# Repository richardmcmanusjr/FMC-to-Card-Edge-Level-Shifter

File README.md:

# FMC-to-Card-Edge-Level-Shifter

This repository contains an 88 channel conversion board designed to interface an 88-pin probe card with a Virtex-7 VC707 FPGA via an FMC cable. Level shifting was required to lower the FPGA's 1.8V logic to 1.2V. Resistor voltage dividers were chosen for this purpose.

# V3.1

- Resistor arrays used for voltage dividers
- Male header pins oriented at right angle to FMC connector
- Low quiescent current regulator implemented for 1.2V power supply
- Jumper for selecting power from FPGA or SMA

## Design

## Layout 

# V2

- Discrete 0603 resistors used for voltage dividers
- Card edge connector oriented at right angle to FMC connector
- Optional SMAs for GND and Power
 
## Design

## Layout

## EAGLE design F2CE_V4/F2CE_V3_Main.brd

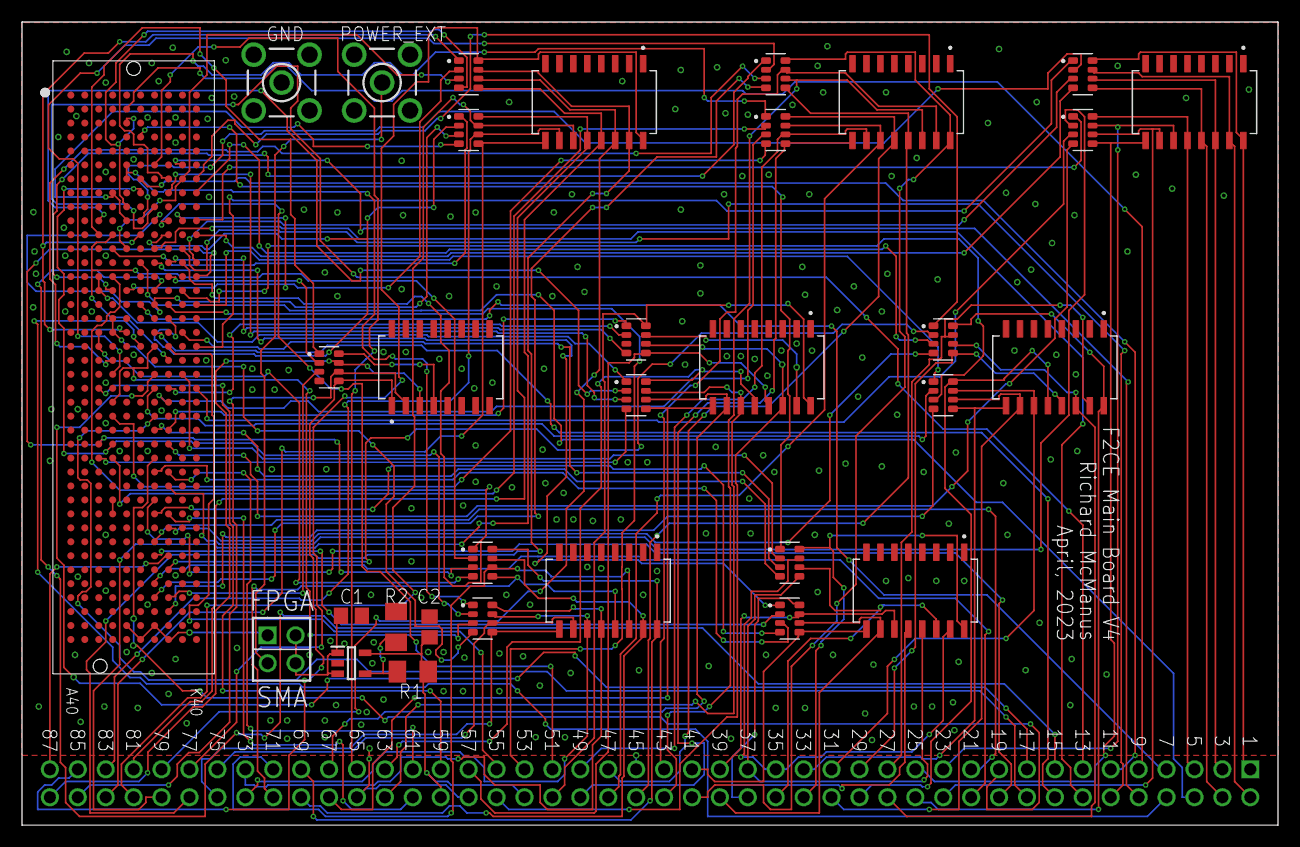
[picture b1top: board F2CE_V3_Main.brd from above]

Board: 2 copper layers, 114.3 x 73.1 mm, 33 parts (0 on the bottom side), 150 nets.

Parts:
4BITVD1:R1, 8BITVD1:R1, 8BITVD1:R2, 8BITVD2:R1, 8BITVD2:R2, 8BITVD3:R1, 8BITVD3:R2, 8BITVD4:R1, 8BITVD4:R2, 8BITVD5:R1, 8BITVD5:R2, 8BITVD6:R1, 8BITVD6:R2, 8BITVD7:R1, 8BITVD7:R2: YC164-FR-0760R4L; RESCAXE80P320X160X70-8N
4BITVD1:RN1, 8BITVD1:RN1, 8BITVD2:RN1, 8BITVD3:RN1, 8BITVD4:RN1, 8BITVD5:RN1, 8BITVD6:RN1, 8BITVD7:RN1: 4816P-1-121LF; SOIC127P762X240-16N
C1, C2: 1 uF; C0805
GND: LTI-SASF54GT
IC1: ADP171AUJZ-R7; SOT95P280X100-5N
J1: 88-PIN-HEADER
J2: ASP-134602-01; ASP13460201
J3: 70287-1098; HDRV4W64P254_2X2_521X508X851P
POWER_EXT: LTI-SASF54GT
R1: 510; M1206
R2: 360; M1206

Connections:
4BITVD1:OUT3: 4BITVD1:R1.8, 4BITVD1:RN1.4
8BITVD5:OUT1: 8BITVD5:R1.7, 8BITVD5:RN1.15
C10: 8BITVD5:R2.2, J2.C10
C11: 4BITVD1:R1.1, J2.C11
C14&C15: 8BITVD5:R2.1, J2.C14, J2.C15
C18&C19: 8BITVD6:R1.4, J2.C18, J2.C19
C22: J1.59, J2.C22
C26&K14: 8BITVD6:R1.3, J2.C26, J2.K14
C27: 8BITVD5:R2.4, J2.C27
CS10: 8BITVD5:R2.6, 8BITVD5:RN1.10, J1.67
CS11: 4BITVD1:R1.5, 4BITVD1:RN1.1, J1.85
CS14&CS15: 8BITVD5:R2.5, 8BITVD5:RN1.9, J1.68
CS18&CS19: 8BITVD6:R1.8, 8BITVD6:RN1.16, J1.69
CS26&KS14: 8BITVD6:R1.7, 8BITVD6:RN1.15, J1.70
CS27: 8BITVD5:R2.8, 8BITVD5:RN1.12, J1.63
D8&E10: 8BITVD7:R2.4, J2.D8, J2.E10
D11&H20: 8BITVD6:R1.2, J2.D11, J2.H20
D12: 8BITVD7:R2.1, J2.D12
D14&J13: 8BITVD6:R1.1, J2.D14, J2.J13
D15: 8BITVD4:R1.1, J2.D15
D17&D18: 8BITVD6:R2.4, J2.D17, J2.D18
D20: 8BITVD4:R1.3, J2.D20
D21: 8BITVD4:R1.2, J2.D21
D23&G19: 8BITVD6:R2.3, J2.D23, J2.G19
D24: 8BITVD4:R2.4, J2.D24
D26&F8: 8BITVD6:R2.2, J2.D26, J2.F8
D27: 8BITVD4:R2.2, J2.D27
DS8&ES10: 8BITVD7:R2.8, 8BITVD7:RN1.12, J1.81
DS11&HS20: 8BITVD6:R1.6, 8BITVD6:RN1.14, J1.71
DS12: 8BITVD7:R2.5, 8BITVD7:RN1.9, J1.84
DS14&JS13: 8BITVD6:R1.5, 8BITVD6:RN1.13, J1.72
DS15: 8BITVD4:R1.5, 8BITVD4:RN1.13, J1.46
DS17&DS18: 8BITVD6:R2.8, 8BITVD6:RN1.12, J1.73
DS20: 8BITVD4:R1.7, 8BITVD4:RN1.15, J1.43
DS21: 8BITVD4:R1.6, 8BITVD4:RN1.14, J1.44
DS23&GS19: 8BITVD6:R2.7, 8BITVD6:RN1.11, J1.74
DS24: 8BITVD4:R2.8, 8BITVD4:RN1.12, J1.47
DS26&FS8: 8BITVD6:R2.6, 8BITVD6:RN1.10, J1.75
DS27: 8BITVD4:R2.6, 8BITVD4:RN1.10, J1.49
E2: J1.9, J2.E2
E6&E7: 8BITVD6:R2.1, J2.E6, J2.E7
E9&E3: 8BITVD7:R1.4, J2.E3, J2.E9
E12&J7: 8BITVD7:R1.3, J2.E12, J2.J7
E15&J10: 8BITVD7:R1.2, J2.E15, J2.J10
E18&F11: 8BITVD7:R1.1, J2.E18, J2.F11
ES6&ES7: 8BITVD6:R2.5, 8BITVD6:RN1.9, J1.76
ES9&ES3: 8BITVD7:R1.8, 8BITVD7:RN1.16, J1.77
ES12&JS7: 8BITVD7:R1.7, 8BITVD7:RN1.15, J1.78
ES15&JS10: 8BITVD7:R1.6, 8BITVD7:RN1.14, J1.79
ES18&FS11: 8BITVD7:R1.5, 8BITVD7:RN1.13, J1.80
F4: 8BITVD3:R1.1, J2.F4
F7: J1.11, J2.F7
F10: 8BITVD1:R1.2, J2.F10
F13: J1.6, J2.F13
F16: J1.7, J2.F16
F19: J1.8, J2.F19
FS4: 8BITVD3:R1.5, 8BITVD3:RN1.13, J1.37
FS10: 8BITVD1:R1.6, 8BITVD1:RN1.14, J1.3
G6: J1.65, J2.G6
G9: J1.13, J2.G9
G10&G16: 8BITVD7:R2.3, J2.G10, J2.G16
G12: J1.14, J2.G12
G13: 8BITVD3:R2.1, J2.G13
G15: J1.15, J2.G15
G18: J1.16, J2.G18
G21: J1.17, J2.G21
G22: 8BITVD2:R2.2, J2.G22
G24: J1.18, J2.G24
G25: 8BITVD3:R1.4, J2.G25
G27: J1.19, J2.G27
G28: 8BITVD3:R2.3, J2.G28
G30: J1.20, J2.G30
G31: 8BITVD3:R2.4, J2.G31
G33: J1.21, J2.G33
G34: 8BITVD3:R2.2, J2.G34
G36: J1.22, J2.G36
G37: 8BITVD4:R1.4, J2.G37
GND: 4BITVD1:RN1.13, 4BITVD1:RN1.14, 4BITVD1:RN1.15, 4BITVD1:RN1.16, 8BITVD1:RN1.1, 8BITVD1:RN1.2, 8BITVD1:RN1.3, 8BITVD1:RN1.4, 8BITVD1:RN1.5, 8BITVD1:RN1.6, 8BITVD1:RN1.7, 8BITVD1:RN1.8, 8BITVD2:RN1.1, 8BITVD2:RN1.2, 8BITVD2:RN1.3, 8BITVD2:RN1.4, 8BITVD2:RN1.5, 8BITVD2:RN1.6, 8BITVD2:RN1.7, 8BITVD2:RN1.8, 8BITVD3:RN1.1, 8BITVD3:RN1.2, 8BITVD3:RN1.3, 8BITVD3:RN1.4, 8BITVD3:RN1.5, 8BITVD3:RN1.6, 8BITVD3:RN1.7, 8BITVD3:RN1.8, 8BITVD4:RN1.1, 8BITVD4:RN1.2, 8BITVD4:RN1.3, 8BITVD4:RN1.4, 8BITVD4:RN1.5, 8BITVD4:RN1.6, 8BITVD4:RN1.7, 8BITVD4:RN1.8, 8BITVD5:RN1.1, 8BITVD5:RN1.2, 8BITVD5:RN1.3, 8BITVD5:RN1.4, 8BITVD5:RN1.5, 8BITVD5:RN1.6, 8BITVD5:RN1.7, 8BITVD5:RN1.8, 8BITVD6:RN1.1, 8BITVD6:RN1.2, 8BITVD6:RN1.3, 8BITVD6:RN1.4, 8BITVD6:RN1.5, 8BITVD6:RN1.6, 8BITVD6:RN1.7, 8BITVD6:RN1.8, 8BITVD7:RN1.1, 8BITVD7:RN1.2, 8BITVD7:RN1.3, 8BITVD7:RN1.4, 8BITVD7:RN1.5, 8BITVD7:RN1.6, 8BITVD7:RN1.7, 8BITVD7:RN1.8, C1.2, C2.2, GND.1, GND.2, GND.3, GND.4, GND.5, IC1.2, J1.45, J1.58, J1.66, J2.A4, J2.A5, J2.A8, J2.A9, J2.A12, J2.A13, J2.A16, J2.A17, J2.A20, J2.A21, J2.A24, J2.A25, J2.A28, J2.A29, J2.A32, J2.A33, J2.A36, J2.A37, J2.A40, J2.B2, J2.B3, J2.B6, J2.B7, J2.B18, J2.B19, J2.B22, J2.B23, J2.B26, J2.B27, J2.B30, J2.B31, J2.B34, J2.B35, J2.B38, J2.B39, J2.C1, J2.C4, J2.C5, J2.C8, J2.C9, J2.C12, J2.C13, J2.C16, J2.C20, J2.C21, J2.C24, J2.C25, J2.C28, J2.C29, J2.C32, J2.C33, J2.C36, J2.C38, J2.C40, J2.D2, J2.D3, J2.D13, J2.D16, J2.D25, J2.D28, J2.D37, J2.D39, J2.E1, J2.E4, J2.E5, J2.E14, J2.E26, J2.E32, J2.E40, J2.F2, J2.F3, J2.F15, J2.F18, J2.F39, J2.G1, J2.G4, J2.G5, J2.G17, J2.G26, J2.G38, J2.G40, J2.H3, J2.H6, J2.H18, J2.H21, J2.H27, J2.H39, J2.J1, J2.J4, J2.J5, J2.J20, J2.J23, J2.J35, J2.J40, J2.K2, J2.K3, J2.K6, J2.K21, J2.K36, POWER_EXT.2, POWER_EXT.3, POWER_EXT.4, POWER_EXT.5, R2.1
GS10&GS16: 8BITVD7:R2.7, 8BITVD7:RN1.11, J1.82
GS13: 8BITVD3:R2.5, 8BITVD3:RN1.9, J1.41
GS22: 8BITVD2:R2.6, 8BITVD2:RN1.10, J1.32
GS25: 8BITVD3:R1.8, 8BITVD3:RN1.16, J1.34
GS28: 8BITVD3:R2.7, 8BITVD3:RN1.11, J1.39
GS31: 8BITVD3:R2.8, 8BITVD3:RN1.12, J1.38
GS34: 8BITVD3:R2.6, 8BITVD3:RN1.10, J1.40
GS37: 8BITVD4:R1.8, 8BITVD4:RN1.16, J1.42
H7: 8BITVD4:R2.1, J2.H7
H8: 8BITVD5:R2.3, J2.H8
H10: J1.51, J2.H10
H11&H17: 8BITVD7:R2.2, J2.H11, J2.H17
H13: 8BITVD5:R1.4, J2.H13
H14: 4BITVD1:R1.2, J2.H14
H16: J1.53, J2.H16
H19: J1.55, J2.H19
H22: 8BITVD5:R1.2, J2.H22
H23: 8BITVD4:R2.3, J2.H23
H25: 8BITVD5:R1.1, J2.H25
H26: 8BITVD1:R2.4, J2.H26
H28: J1.61, J2.H28
H29: 8BITVD1:R2.2, J2.H29
H31: J1.62, J2.H31
H32: 8BITVD2:R1.4, J2.H32
H34: J1.87, J2.H34
H35: 8BITVD2:R1.2, J2.H35
H37: 4BITVD1:R1.3, J2.H37
H38: 8BITVD2:R2.4, J2.H38
HS7: 8BITVD4:R2.5, 8BITVD4:RN1.9, J1.50
HS8: 8BITVD5:R2.7, 8BITVD5:RN1.11, J1.64
HS11&HS17: 8BITVD7:R2.6, 8BITVD7:RN1.10, J1.83
HS13: 8BITVD5:R1.8, 8BITVD5:RN1.16, J1.52
HS14: 4BITVD1:R1.6, 4BITVD1:RN1.2, J1.86
HS22: 8BITVD5:R1.6, 8BITVD5:RN1.14, J1.56
HS23: 8BITVD4:R2.7, 8BITVD4:RN1.11, J1.48
HS25: 8BITVD5:R1.5, 8BITVD5:RN1.13, J1.57
HS26: 8BITVD1:R2.8, 8BITVD1:RN1.12, J1.5
HS29: 8BITVD1:R2.6, 8BITVD1:RN1.10, J1.24
HS32: 8BITVD2:R1.8, 8BITVD2:RN1.16, J1.26
HS35: 8BITVD2:R1.6, 8BITVD2:RN1.14, J1.28
HS37: 4BITVD1:R1.7, 4BITVD1:RN1.3, J1.88
HS38: 8BITVD2:R2.8, 8BITVD2:RN1.12, J1.30
J6: J1.10, J2.J6
J12: J1.12, J2.J12
J15: 8BITVD2:R2.3, J2.J15
J18: 8BITVD3:R1.3, J2.J18
J21: 8BITVD3:R1.2, J2.J21
JS15: 8BITVD2:R2.7, 8BITVD2:RN1.11, J1.31
JS18: 8BITVD3:R1.7, 8BITVD3:RN1.15, J1.35
JS21: 8BITVD3:R1.6, 8BITVD3:RN1.14, J1.36
K7: 8BITVD2:R1.1, J2.K7
K8: 8BITVD2:R1.3, J2.K8
K10: 8BITVD1:R2.1, J2.K10
K11: 8BITVD1:R1.4, J2.K11
K13: 8BITVD1:R1.3, J2.K13
K16: 8BITVD2:R2.1, J2.K16
K19: 8BITVD1:R1.1, J2.K19
K22: 8BITVD1:R2.3, J2.K22
KS7: 8BITVD2:R1.5, 8BITVD2:RN1.13, J1.29
KS8: 8BITVD2:R1.7, 8BITVD2:RN1.15, J1.27
KS10: 8BITVD1:R2.5, 8BITVD1:RN1.9, J1.25
KS11: 8BITVD1:R1.8, 8BITVD1:RN1.16, J1.1
KS13: 8BITVD1:R1.7, 8BITVD1:RN1.15, J1.2
KS16: 8BITVD2:R2.5, 8BITVD2:RN1.9, J1.33
KS19: 8BITVD1:R1.5, 8BITVD1:RN1.13, J1.4
KS22: 8BITVD1:R2.7, 8BITVD1:RN1.11, J1.23
unnamed: C1.1, IC1.1, IC1.3, J3.2, J3.4
unnamed: J2.D30, J2.D31
unnamed: IC1.4, R1.2, R2.2
POWER_EXT: J3.3, POWER_EXT.1
POWER_FPGA: J2.E39, J2.F40, J2.G39, J2.H40, J3.1
VDD: C2.1, IC1.5, J1.54, J1.60, R1.1

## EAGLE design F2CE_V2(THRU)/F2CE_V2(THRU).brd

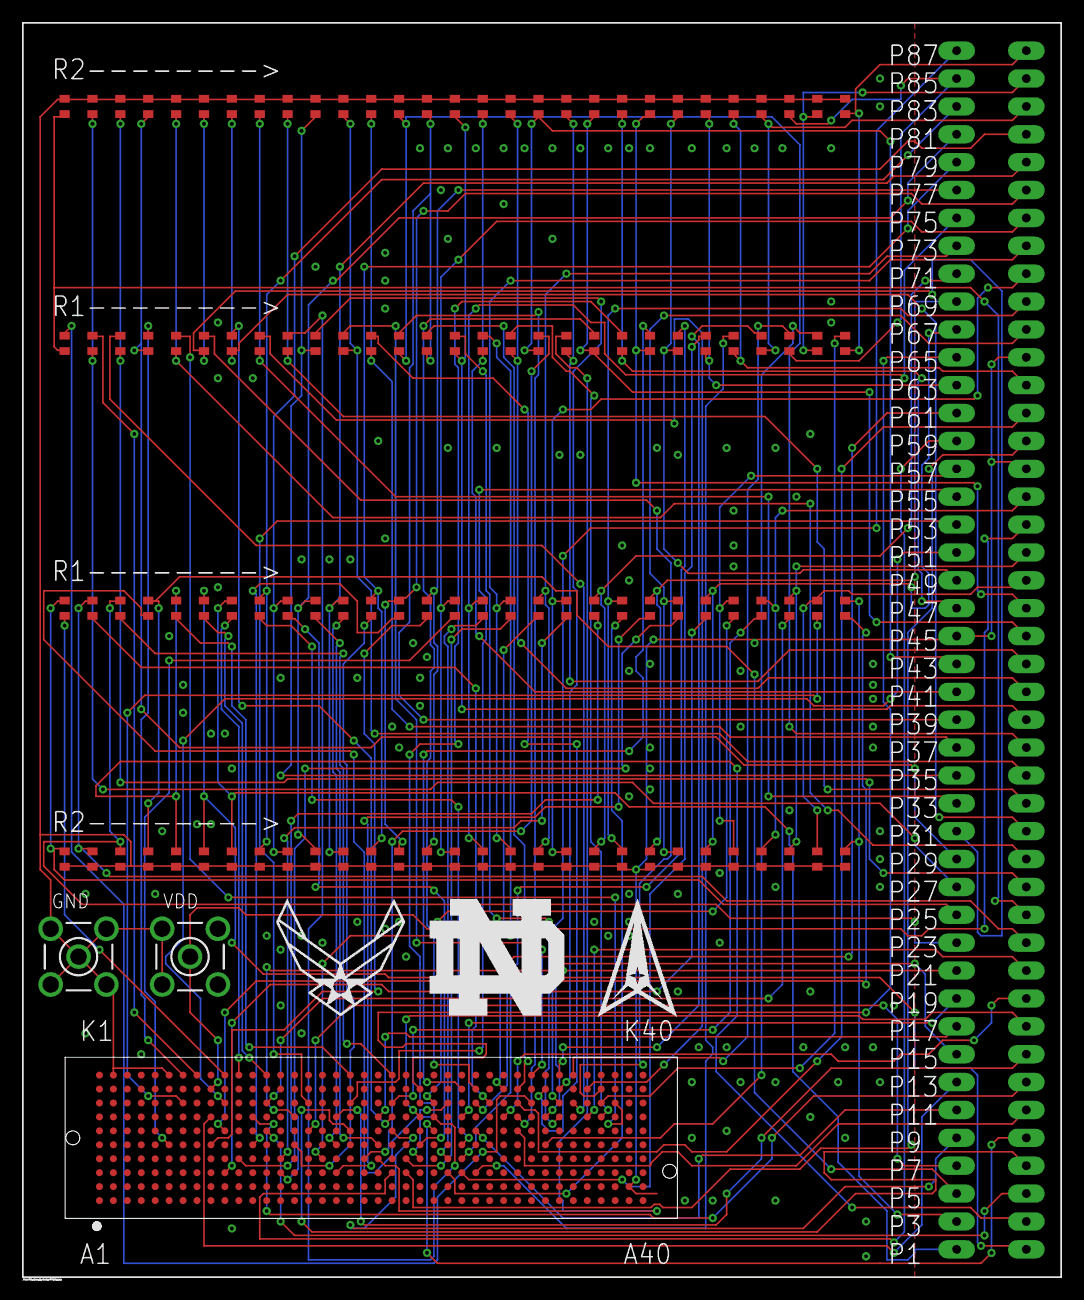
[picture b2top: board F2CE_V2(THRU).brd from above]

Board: 2 copper layers, 94.6 x 114.3 mm, 120 parts (0 on the bottom side), 144 nets.

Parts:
GND: LTI-SASF54GT
J1: ASP-134602-01; ASP13460201
U$1: EDGEPADS(THRU)
VD1:R1, VD1:R2, VD2:R1, VD2:R2, VD3:R1, VD3:R2, VD4:R1, VD4:R2, VD5:R1, VD5:R2, VD6:R1, VD6:R2, VD7:R1, VD7:R2, VD8:R1, VD8:R2, VD9:R1, VD9:R2, VD10:R1, VD10:R2, VD11:R1, VD11:R2, VD12:R1, VD12:R2, VD13:R1, VD13:R2, VD14:R1, VD14:R2, VD15:R1, VD15:R2, VD16:R1, VD16:R2, VD17:R1, VD17:R2, VD18:R1, VD18:R2, VD19:R1, VD19:R2, VD20:R1, VD20:R2, VD21:R1, VD21:R2, VD22:R1, VD22:R2, VD23:R1, VD23:R2, VD24:R1, VD24:R2, VD25:R1, VD25:R2, VD26:R1, VD26:R2, VD27:R1, VD27:R2, VD28:R1, VD28:R2, VD29:R1, VD29:R2, VD30:R1, VD30:R2, VD31:R1, VD31:R2, VD32:R1, VD32:R2, VD33:R1, VD33:R2, VD34:R1, VD34:R2, VD35:R1, VD35:R2, VD36:R1, VD36:R2, VD37:R1, VD37:R2, VD38:R1, VD38:R2, VD39:R1, VD39:R2, VD40:R1, VD40:R2, VD41:R1, VD41:R2, VD42:R1, VD42:R2, VD43:R1, VD43:R2, VD44:R1, VD44:R2, VD45:R1, VD45:R2, VD46:R1, VD46:R2, VD47:R1, VD47:R2, VD48:R1, VD48:R2, VD49:R1, VD49:R2, VD50:R1, VD50:R2, VD51:R1, VD51:R2, VD52:R1, VD52:R2, VD53:R1, VD53:R2, VD54:R1, VD54:R2, VD55:R1, VD55:R2, VD56:R1, VD56:R2, VD57:R1, VD57:R2, VD58:R1, VD58:R2: RMCF0603ZT0R00; STA_RMCF0603_STP
VDD: LTI-SASF54GT

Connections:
C10: J1.C10, VD6:R1.1
C14: J1.C14, VD7:R1.1
C18: J1.C18, VD8:R1.1
C22: J1.C22, U$1.P$59
C23: J1.C23, U$1.P$60
C26: J1.C26, VD9:R1.1
C27: J1.C27, VD53:R1.1
C28: J1.C28, VD54:R1.1
CS10: U$1.P$67, VD6:R1.2, VD6:R2.2
CS14: U$1.P$68, VD7:R1.2, VD7:R2.2
CS18: U$1.P$69, VD8:R1.2, VD8:R2.2
CS26: U$1.P$70, VD9:R1.2, VD9:R2.2
CS27: U$1.P$63, VD53:R1.2, VD53:R2.2
CS28: U$1.P$64, VD54:R1.2, VD54:R2.2
D11: J1.D11, VD10:R1.1
D14: J1.D14, VD11:R1.1
D17: J1.D17, VD12:R1.1
D20: J1.D20, VD47:R1.1
D21: J1.D21, VD48:R1.1
D23: J1.D23, VD13:R1.1
D24: J1.D24, VD50:R1.1
D26: J1.D26, VD14:R1.1
D27: J1.D27, VD52:R1.1
DS11: U$1.P$71, VD10:R1.2, VD10:R2.2
DS14: U$1.P$72, VD11:R1.2, VD11:R2.2
DS17: U$1.P$73, VD12:R1.2, VD12:R2.2
DS20: U$1.P$43, VD47:R1.2, VD47:R2.2
DS21: U$1.P$44, VD48:R1.2, VD48:R2.2
DS23: U$1.P$74, VD13:R1.2, VD13:R2.2
DS24: U$1.P$47, VD50:R1.2, VD50:R2.2
DS26: U$1.P$75, VD14:R1.2, VD14:R2.2
DS27: U$1.P$49, VD52:R1.2, VD52:R2.2
E6: J1.E6, VD15:R1.1
E9: J1.E9, VD16:R1.1
E12: J1.E12, VD17:R1.1
E15: J1.E15, VD18:R1.1
E18: J1.E18, VD19:R1.1
E21: J1.E21, VD20:R1.1
E24: J1.E24, VD21:R1.1
E27: J1.E27, VD22:R1.1
E33: J1.E33, VD57:R1.1
ES6: U$1.P$76, VD15:R1.2, VD15:R2.2
ES9: U$1.P$77, VD16:R1.2, VD16:R2.2
ES12: U$1.P$78, VD17:R1.2, VD17:R2.2
ES15: U$1.P$79, VD18:R1.2, VD18:R2.2
ES18: U$1.P$80, VD19:R1.2, VD19:R2.2
ES21: U$1.P$81, VD20:R1.2, VD20:R2.2
ES24: U$1.P$82, VD21:R1.2, VD21:R2.2
ES27: U$1.P$83, VD22:R1.2, VD22:R2.2
ES33: U$1.P$86, VD57:R1.2, VD57:R2.2
F10: J1.F10, VD1:R1.1
F13: J1.F13, U$1.P$6
F16: J1.F16, U$1.P$7
F19: J1.F19, U$1.P$8
F22: J1.F22, U$1.P$9
F25: J1.F25, U$1.P$10
F28: J1.F28, U$1.P$11
F31: J1.F31, U$1.P$12
FS10: U$1.P$3, VD1:R1.2, VD1:R2.2
G9: J1.G9, U$1.P$13
G12: J1.G12, U$1.P$14
G15: J1.G15, U$1.P$15
G18: J1.G18, U$1.P$16
G21: J1.G21, U$1.P$17
G22: J1.G22, VD36:R1.1
G24: J1.G24, U$1.P$18
G25: J1.G25, VD38:R1.1
G27: J1.G27, U$1.P$19
G30: J1.G30, U$1.P$20
G31: J1.G31, VD42:R1.1
G33: J1.G33, U$1.P$21
G34: J1.G34, VD44:R1.1
G36: J1.G36, U$1.P$22
G37: J1.G37, VD46:R1.1
GND: GND.1, GND.2, GND.3, GND.4, GND.5, J1.B39, J1.K2, J1.K6, U$1.P$45, U$1.P$58, U$1.P$66, VD1:R2.1, VD2:R2.1, VD3:R2.1, VD4:R2.1, VD5:R2.1, VD6:R2.1, VD7:R2.1, VD8:R2.1, VD9:R2.1, VD10:R2.1, VD11:R2.1, VD12:R2.1, VD13:R2.1, VD14:R2.1, VD15:R2.1, VD16:R2.1, VD17:R2.1, VD18:R2.1, VD19:R2.1, VD20:R2.1, VD21:R2.1, VD22:R2.1, VD23:R2.1, VD24:R2.1, VD25:R2.1, VD26:R2.1, VD27:R2.1, VD28:R2.1, VD29:R2.1, VD30:R2.1, VD31:R2.1, VD32:R2.1, VD33:R2.1, VD34:R2.1, VD35:R2.1, VD36:R2.1, VD37:R2.1, VD38:R2.1, VD39:R2.1, VD40:R2.1, VD41:R2.1, VD42:R2.1, VD43:R2.1, VD44:R2.1, VD45:R2.1, VD46:R2.1, VD47:R2.1, VD48:R2.1, VD49:R2.1, VD50:R2.1, VD51:R2.1, VD52:R2.1, VD53:R2.1, VD54:R2.1, VD55:R2.1, VD56:R2.1, VD57:R2.1, VD58:R2.1, VDD.2, VDD.3, VDD.4, VDD.5
GS22: U$1.P$32, VD36:R1.2, VD36:R2.2
GS25: U$1.P$34, VD38:R1.2, VD38:R2.2
GS31: U$1.P$38, VD42:R1.2, VD42:R2.2
GS34: U$1.P$40, VD44:R1.2, VD44:R2.2
GS37: U$1.P$42, VD46:R1.2, VD46:R2.2
H7: J1.H7, VD2:R1.1
H10: J1.H10, U$1.P$51
H13: J1.H13, VD3:R1.1
H16: J1.H16, U$1.P$53
H19: J1.H19, U$1.P$55
H22: J1.H22, VD4:R1.1
H25: J1.H25, VD5:R1.1
H26: J1.H26, VD26:R1.1
H28: J1.H28, U$1.P$61
H29: J1.H29, VD28:R1.1
H31: J1.H31, U$1.P$62
H32: J1.H32, VD30:R1.1
H34: J1.H34, U$1.P$87
H35: J1.H35, VD32:R1.1
H37: J1.H37, VD58:R1.1
H38: J1.H38, VD34:R1.1
HS7: U$1.P$50, VD2:R1.2, VD2:R2.2
HS13: U$1.P$52, VD3:R1.2, VD3:R2.2
HS22: U$1.P$56, VD4:R1.2, VD4:R2.2
HS25: U$1.P$57, VD5:R1.2, VD5:R2.2
HS26: U$1.P$5, VD26:R1.2, VD26:R2.2
HS29: U$1.P$24, VD28:R1.2, VD28:R2.2
HS32: U$1.P$26, VD30:R1.2, VD30:R2.2
HS35: U$1.P$28, VD32:R1.2, VD32:R2.2
HS37: U$1.P$88, VD58:R1.2, VD58:R2.2
HS38: U$1.P$30, VD34:R1.2, VD34:R2.2
J24: J1.J24, U$1.P$65
J27: J1.J27, VD51:R1.1
J28: J1.J28, VD49:R1.1
J30: J1.J30, VD45:R1.1
J31: J1.J31, VD43:R1.1
J33: J1.J33, VD41:R1.1
J34: J1.J34, VD39:R1.1
J36: J1.J36, VD37:R1.1
J37: J1.J37, VD35:R1.1
JS27: U$1.P$48, VD51:R1.2, VD51:R2.2
JS28: U$1.P$46, VD49:R1.2, VD49:R2.2
JS30: U$1.P$41, VD45:R1.2, VD45:R2.2
JS31: U$1.P$39, VD43:R1.2, VD43:R2.2
JS33: U$1.P$37, VD41:R1.2, VD41:R2.2
JS34: U$1.P$35, VD39:R1.2, VD39:R2.2
JS36: U$1.P$33, VD37:R1.2, VD37:R2.2
JS37: U$1.P$31, VD35:R1.2, VD35:R2.2
K7: J1.K7, VD33:R1.1
K8: J1.K8, VD31:R1.1
K10: J1.K10, VD29:R1.1
K11: J1.K11, VD23:R1.1
K13: J1.K13, VD24:R1.1
K19: J1.K19, VD25:R1.1
K22: J1.K22, VD27:R1.1
K32: J1.K32, VD40:R1.1
K34: J1.K34, VD55:R1.1
K35: J1.K35, VD56:R1.1
KS7: U$1.P$29, VD33:R1.2, VD33:R2.2
KS8: U$1.P$27, VD31:R1.2, VD31:R2.2
KS10: U$1.P$25, VD29:R1.2, VD29:R2.2
KS11: U$1.P$1, VD23:R1.2, VD23:R2.2
KS13: U$1.P$2, VD24:R1.2, VD24:R2.2
KS19: U$1.P$4, VD25:R1.2, VD25:R2.2
KS22: U$1.P$23, VD27:R1.2, VD27:R2.2
KS32: U$1.P$36, VD40:R1.2, VD40:R2.2
KS34: U$1.P$84, VD55:R1.2, VD55:R2.2
KS35: U$1.P$85, VD56:R1.2, VD56:R2.2
VDD: J1.J9, U$1.P$54, VDD.1

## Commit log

2023-02-04 Create temp
2023-02-04 Updated SMA Connections
2023-02-05 Upload Documentation
2023-02-05 Updated Block Diagram
2023-02-16 Upload Second Board
2023-03-01 Added files via upload
2023-03-17 Renamed versions
2023-03-27 Added libraries
2023-03-27 Updated Photo
2023-03-28 Renamed

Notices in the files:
parts and their libraries:
COPYRIGHT: Copyright (C) 2022 Ultra Librarian. All rights reserved.
